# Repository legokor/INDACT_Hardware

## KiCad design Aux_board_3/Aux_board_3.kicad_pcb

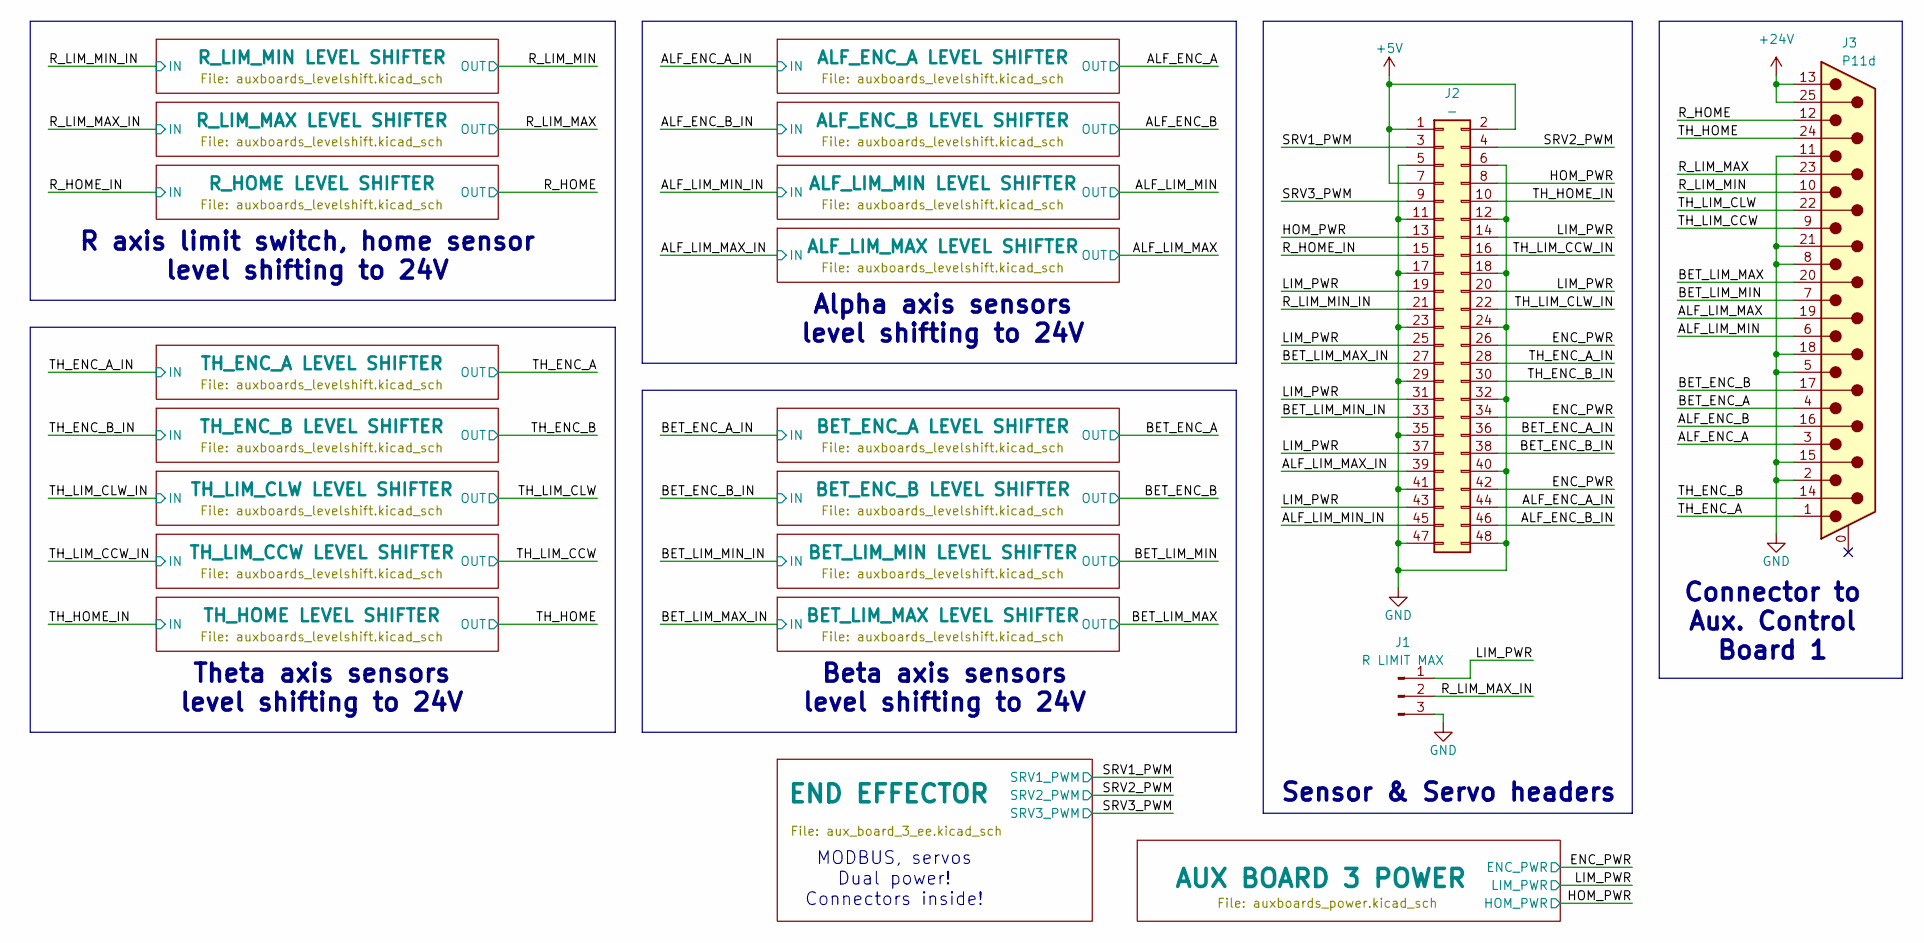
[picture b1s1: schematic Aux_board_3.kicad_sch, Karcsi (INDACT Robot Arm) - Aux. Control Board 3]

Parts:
J1: R LIMIT MAX; PinHeader_1x03_P2.54mm_Horizontal
J2: -; PinHeader_2x24_P2.54mm_Horizontal
J3: P11d; DSUB-25_Male_Horizontal_P2.77x2.84mm_EdgePinOffset7.70mm_Ho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

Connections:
+5V: J2.1, J2.2, J2.7; also elsewhere on the board
+24V: J3.13, J3.25; also elsewhere on the board
/ALF_ENC_A: J3.3; also elsewhere on the board
/ALF_ENC_A_IN: J2.44; also elsewhere on the board
/ALF_ENC_B: J3.16; also elsewhere on the board
/ALF_ENC_B_IN: J2.46; also elsewhere on the board
/ALF_LIM_MAX: J3.19; also elsewhere on the board
/ALF_LIM_MAX_IN: J2.39; also elsewhere on the board
/ALF_LIM_MIN: J3.6; also elsewhere on the board
/ALF_LIM_MIN_IN: J2.45; also elsewhere on the board
/BET_ENC_A: J3.4; also elsewhere on the board
/BET_ENC_A_IN: J2.36; also elsewhere on the board
/BET_ENC_B: J3.17; also elsewhere on the board
/BET_ENC_B_IN: J2.38; also elsewhere on the board
/BET_LIM_MAX: J3.20; also elsewhere on the board
/BET_LIM_MAX_IN: J2.27; also elsewhere on the board
/BET_LIM_MIN: J3.7; also elsewhere on the board
/BET_LIM_MIN_IN: J2.33; also elsewhere on the board
/ENC_PWR: J2.26, J2.34, J2.42; also elsewhere on the board
/HOM_PWR: J2.8, J2.13; also elsewhere on the board
/LIM_PWR: J1.1, J2.14, J2.19, J2.20, J2.25, J2.31, J2.37, J2.43; also elsewhere on the board
/R_HOME: J3.12; also elsewhere on the board
/R_HOME_IN: J2.15; also elsewhere on the board
/R_LIM_MAX: J3.23; also elsewhere on the board
/R_LIM_MAX_IN: J1.2; also elsewhere on the board
/R_LIM_MIN: J3.10; also elsewhere on the board
/R_LIM_MIN_IN: J2.21; also elsewhere on the board
/SRV1_PWM: J2.3; also elsewhere on the board
/SRV2_PWM: J2.4; also elsewhere on the board
/SRV3_PWM: J2.9; also elsewhere on the board
/TH_ENC_A: J3.1; also elsewhere on the board
/TH_ENC_A_IN: J2.28; also elsewhere on the board
/TH_ENC_B: J3.14; also elsewhere on the board
/TH_ENC_B_IN: J2.30; also elsewhere on the board
/TH_HOME: J3.24; also elsewhere on the board
/TH_HOME_IN: J2.10; also elsewhere on the board
/TH_LIM_CCW: J3.9; also elsewhere on the board
/TH_LIM_CCW_IN: J2.16; also elsewhere on the board
/TH_LIM_CLW: J3.22; also elsewhere on the board
/TH_LIM_CLW_IN: J2.22; also elsewhere on the board
GND: J1.3, J2.5, J2.6, J2.11, J2.12, J2.17, J2.18, J2.23, J2.24, J2.29, J2.32, J2.35, J2.40, J2.41, J2.47, J2.48, J3.2, J3.5, J3.8, J3.11, J3.15, J3.18, J3.21; also elsewhere on the board

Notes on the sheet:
Beta axis sensors level shifting to 24V
Sensor & Servo headers
Theta axis sensors level shifting to 24V
Alpha axis sensors level shifting to 24V
MODBUS, servos Dual power! Connectors inside!
R axis limit switch, home sensor level shifting to 24V
Connector to Aux. Control Board 1

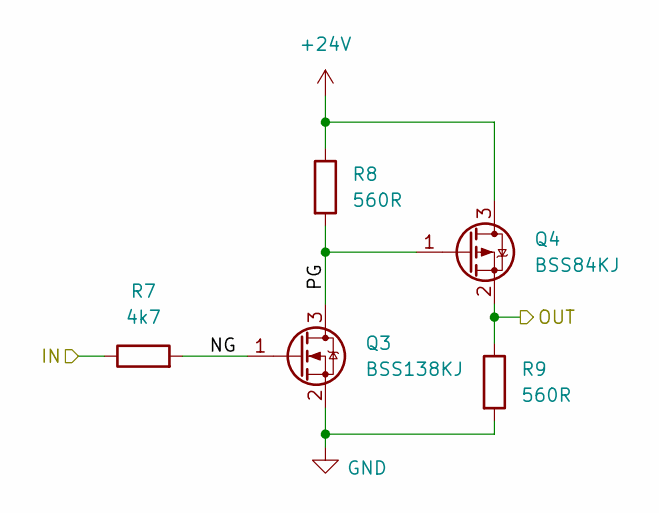
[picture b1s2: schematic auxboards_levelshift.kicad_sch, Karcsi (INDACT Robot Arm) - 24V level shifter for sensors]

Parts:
Q3: BSS138KJ; SOT-23
Q4: BSS84KJ; SOT-23
R7: 4k7; R_0805_2012Metric_Pad1.20x1.40mm_HandSolder
R8, R9: 560R; R_0805_2012Metric_Pad1.20x1.40mm_HandSolder

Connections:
+24V: Q4.3 (D), R8.1; also elsewhere on the board
/ALF_LIM_MIN: Q4.2 (S), R9.1; also elsewhere on the board
/ALF_LIM_MIN LEVEL SHIFTER/NG: Q3.1 (G), R7.2
/ALF_LIM_MIN LEVEL SHIFTER/PG: Q3.3 (D), Q4.1 (G), R8.2
/ALF_LIM_MIN_IN: R7.1; also elsewhere on the board
GND: Q3.2 (S), R9.2; also elsewhere on the board

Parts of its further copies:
Q1, Q5, Q7, Q9, Q11, Q13, Q15, Q17, Q19, Q21, Q23, Q25, Q27, Q29, Q31: BSS138KJ; SOT-23
Q2, Q6, Q8, Q10, Q12, Q14, Q16, Q18, Q20, Q22, Q24, Q26, Q28, Q30, Q32: BSS84KJ; SOT-23
R4, R10, R13, R16, R19, R22, R25, R28, R31, R34, R37, R40, R43, R46, R49: 4k7; R_0805_2012Metric_Pad1.20x1.40mm_HandSolder
R5, R6, R11, R12, R14, R15, R17, R18, R20, R21, R23, R24, R26, R27, R29, R30, R32, R33, R35, R36, R38, R39, R41, R42, R44, R45, R47, R48, R50, R51: 560R; R_0805_2012Metric_Pad1.20x1.40mm_HandSolder

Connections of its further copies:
+24V: Q2.3 (D), Q6.3 (D), Q8.3 (D), Q10.3 (D), Q12.3 (D), Q14.3 (D), Q16.3 (D), Q18.3 (D), Q20.3 (D), Q22.3 (D), Q24.3 (D), Q26.3 (D), Q28.3 (D), Q30.3 (D), Q32.3 (D), R5.1, R11.1, R14.1, R17.1, R20.1, R23.1, R26.1, R29.1, R32.1, R35.1, R38.1, R41.1, R44.1, R47.1, R50.1; also elsewhere on the board
/ALF_ENC_A: Q8.2 (S), R15.1; also elsewhere on the board
/ALF_ENC_A LEVEL SHIFTER/NG: Q7.1 (G), R13.2
/ALF_ENC_A LEVEL SHIFTER/PG: Q7.3 (D), Q8.1 (G), R14.2
/ALF_ENC_A_IN: R13.1; also elsewhere on the board
/ALF_ENC_B: Q6.2 (S), R12.1; also elsewhere on the board
/ALF_ENC_B LEVEL SHIFTER/NG: Q5.1 (G), R10.2
/ALF_ENC_B LEVEL SHIFTER/PG: Q5.3 (D), Q6.1 (G), R11.2
/ALF_ENC_B_IN: R10.1; also elsewhere on the board
/ALF_LIM_MAX: Q2.2 (S), R6.1; also elsewhere on the board
/ALF_LIM_MAX LEVEL SHIFTER/NG: Q1.1 (G), R4.2
/ALF_LIM_MAX LEVEL SHIFTER/PG: Q1.3 (D), Q2.1 (G), R5.2
/ALF_LIM_MAX_IN: R4.1; also elsewhere on the board
/BET_ENC_A: Q10.2 (S), R18.1; also elsewhere on the board
/BET_ENC_A LEVEL SHIFTER/NG: Q9.1 (G), R16.2
/BET_ENC_A LEVEL SHIFTER/PG: Q9.3 (D), Q10.1 (G), R17.2
/BET_ENC_A_IN: R16.1; also elsewhere on the board
/BET_ENC_B: Q12.2 (S), R21.1; also elsewhere on the board
/BET_ENC_B LEVEL SHIFTER/NG: Q11.1 (G), R19.2
/BET_ENC_B LEVEL SHIFTER/PG: Q11.3 (D), Q12.1 (G), R20.2
/BET_ENC_B_IN: R19.1; also elsewhere on the board
/BET_LIM_MAX: Q16.2 (S), R27.1; also elsewhere on the board
/BET_LIM_MAX LEVEL SHIFTER/NG: Q15.1 (G), R25.2
/BET_LIM_MAX LEVEL SHIFTER/PG: Q15.3 (D), Q16.1 (G), R26.2
/BET_LIM_MAX_IN: R25.1; also elsewhere on the board
/BET_LIM_MIN: Q14.2 (S), R24.1; also elsewhere on the board
/BET_LIM_MIN LEVEL SHIFTER/NG: Q13.1 (G), R22.2
/BET_LIM_MIN LEVEL SHIFTER/PG: Q13.3 (D), Q14.1 (G), R23.2
/BET_LIM_MIN_IN: R22.1; also elsewhere on the board
/R_HOME: Q32.2 (S), R51.1; also elsewhere on the board
/R_HOME LEVEL SHIFTER/NG: Q31.1 (G), R49.2
/R_HOME LEVEL SHIFTER/PG: Q31.3 (D), Q32.1 (G), R50.2
/R_HOME_IN: R49.1; also elsewhere on the board
/R_LIM_MAX: Q30.2 (S), R48.1; also elsewhere on the board
/R_LIM_MAX LEVEL SHIFTER/NG: Q29.1 (G), R46.2
/R_LIM_MAX LEVEL SHIFTER/PG: Q29.3 (D), Q30.1 (G), R47.2
/R_LIM_MAX_IN: R46.1; also elsewhere on the board
/R_LIM_MIN: Q28.2 (S), R45.1; also elsewhere on the board
/R_LIM_MIN LEVEL SHIFTER/NG: Q27.1 (G), R43.2
/R_LIM_MIN LEVEL SHIFTER/PG: Q27.3 (D), Q28.1 (G), R44.2
/R_LIM_MIN_IN: R43.1; also elsewhere on the board
/TH_ENC_A: Q18.2 (S), R30.1; also elsewhere on the board
/TH_ENC_A LEVEL SHIFTER/NG: Q17.1 (G), R28.2
/TH_ENC_A LEVEL SHIFTER/PG: Q17.3 (D), Q18.1 (G), R29.2
/TH_ENC_A_IN: R28.1; also elsewhere on the board
/TH_ENC_B: Q20.2 (S), R33.1; also elsewhere on the board
/TH_ENC_B LEVEL SHIFTER/NG: Q19.1 (G), R31.2
/TH_ENC_B LEVEL SHIFTER/PG: Q19.3 (D), Q20.1 (G), R32.2
/TH_ENC_B_IN: R31.1; also elsewhere on the board
/TH_HOME: Q26.2 (S), R42.1; also elsewhere on the board
/TH_HOME LEVEL SHIFTER/NG: Q25.1 (G), R40.2
/TH_HOME LEVEL SHIFTER/PG: Q25.3 (D), Q26.1 (G), R41.2
/TH_HOME_IN: R40.1; also elsewhere on the board
/TH_LIM_CCW: Q24.2 (S), R39.1; also elsewhere on the board
/TH_LIM_CCW LEVEL SHIFTER/NG: Q23.1 (G), R37.2
/TH_LIM_CCW LEVEL SHIFTER/PG: Q23.3 (D), Q24.1 (G), R38.2
/TH_LIM_CCW_IN: R37.1; also elsewhere on the board
/TH_LIM_CLW: Q22.2 (S), R36.1; also elsewhere on the board
/TH_LIM_CLW LEVEL SHIFTER/NG: Q21.1 (G), R34.2
/TH_LIM_CLW LEVEL SHIFTER/PG: Q21.3 (D), Q22.1 (G), R35.2
/TH_LIM_CLW_IN: R34.1; also elsewhere on the board
GND: Q1.2 (S), Q5.2 (S), Q7.2 (S), Q9.2 (S), Q11.2 (S), Q13.2 (S), Q15.2 (S), Q17.2 (S), Q19.2 (S), Q21.2 (S), Q23.2 (S), Q25.2 (S), Q27.2 (S), Q29.2 (S), Q31.2 (S), R6.2, R12.2, R15.2, R18.2, R21.2, R24.2, R27.2, R30.2, R33.2, R36.2, R39.2, R42.2, R45.2, R48.2, R51.2; also elsewhere on the board

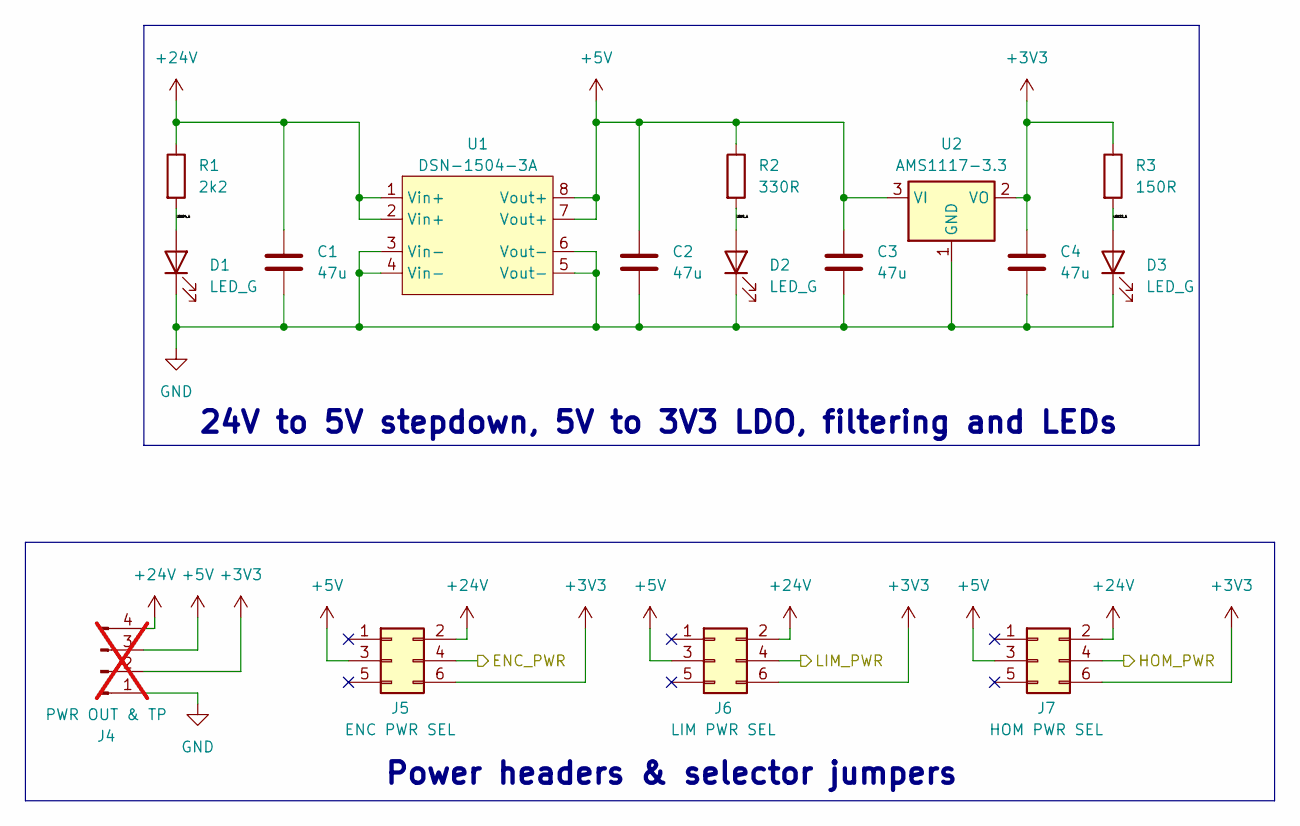
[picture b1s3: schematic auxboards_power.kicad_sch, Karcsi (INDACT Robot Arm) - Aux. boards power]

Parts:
C1, C2, C3, C4: 47u; C_0805_2012Metric_Pad1.18x1.45mm_HandSolder
D1, D2, D3: LED_G; LED_0805_2012Metric_Pad1.15x1.40mm_HandSolder
J4: PWR OUT & TP; PinHeader_1x04_P2.54mm_Vertical; not fitted
J5: ENC PWR SEL; PinHeader_2x03_P2.54mm_Vertical
J6: LIM PWR SEL; PinHeader_2x03_P2.54mm_Vertical
J7: HOM PWR SEL; PinHeader_2x03_P2.54mm_Vertical
R1: 2k2; R_0805_2012Metric_Pad1.20x1.40mm_HandSolder
R2: 330R; R_0805_2012Metric_Pad1.20x1.40mm_HandSolder
R3: 150R; R_0805_2012Metric_Pad1.20x1.40mm_HandSolder
U1: DSN-1504-3A
U2: AMS1117-3.3; SOT-223-3_TabPin2

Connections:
+3V3: C4.1, J4.2, J5.6, J6.6, J7.6, R3.1, U2.2 (VO)
+5V: C2.1, C3.1, J4.3, J5.3, J6.3, J7.3, R2.1, U1.7 (Vout+), U1.8 (Vout+), U2.3 (VI); also elsewhere on the board
+24V: C1.1, J4.4, J5.2, J6.2, J7.2, R1.1, U1.1 (Vin+), U1.2 (Vin+); also elsewhere on the board
/AUX BOARD 3 POWER/LED5_A: D2.2 (A), R2.2
/AUX BOARD 3 POWER/LED24_A: D1.2 (A), R1.2
/AUX BOARD 3 POWER/LED33_A: D3.2 (A), R3.2
/ENC_PWR: J5.4; also elsewhere on the board
/HOM_PWR: J7.4; also elsewhere on the board
/LIM_PWR: J6.4; also elsewhere on the board
GND: C1.2, C2.2, C3.2, C4.2, D1.1 (K), D2.1 (K), D3.1 (K), J4.1, U1.3 (Vin-), U1.4 (Vin-), U1.5 (Vout-), U1.6 (Vout-), U2.1 (GND); also elsewhere on the board

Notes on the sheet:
Power headers & selector jumpers
24V to 5V stepdown, 5V to 3V3 LDO, filtering and LEDs

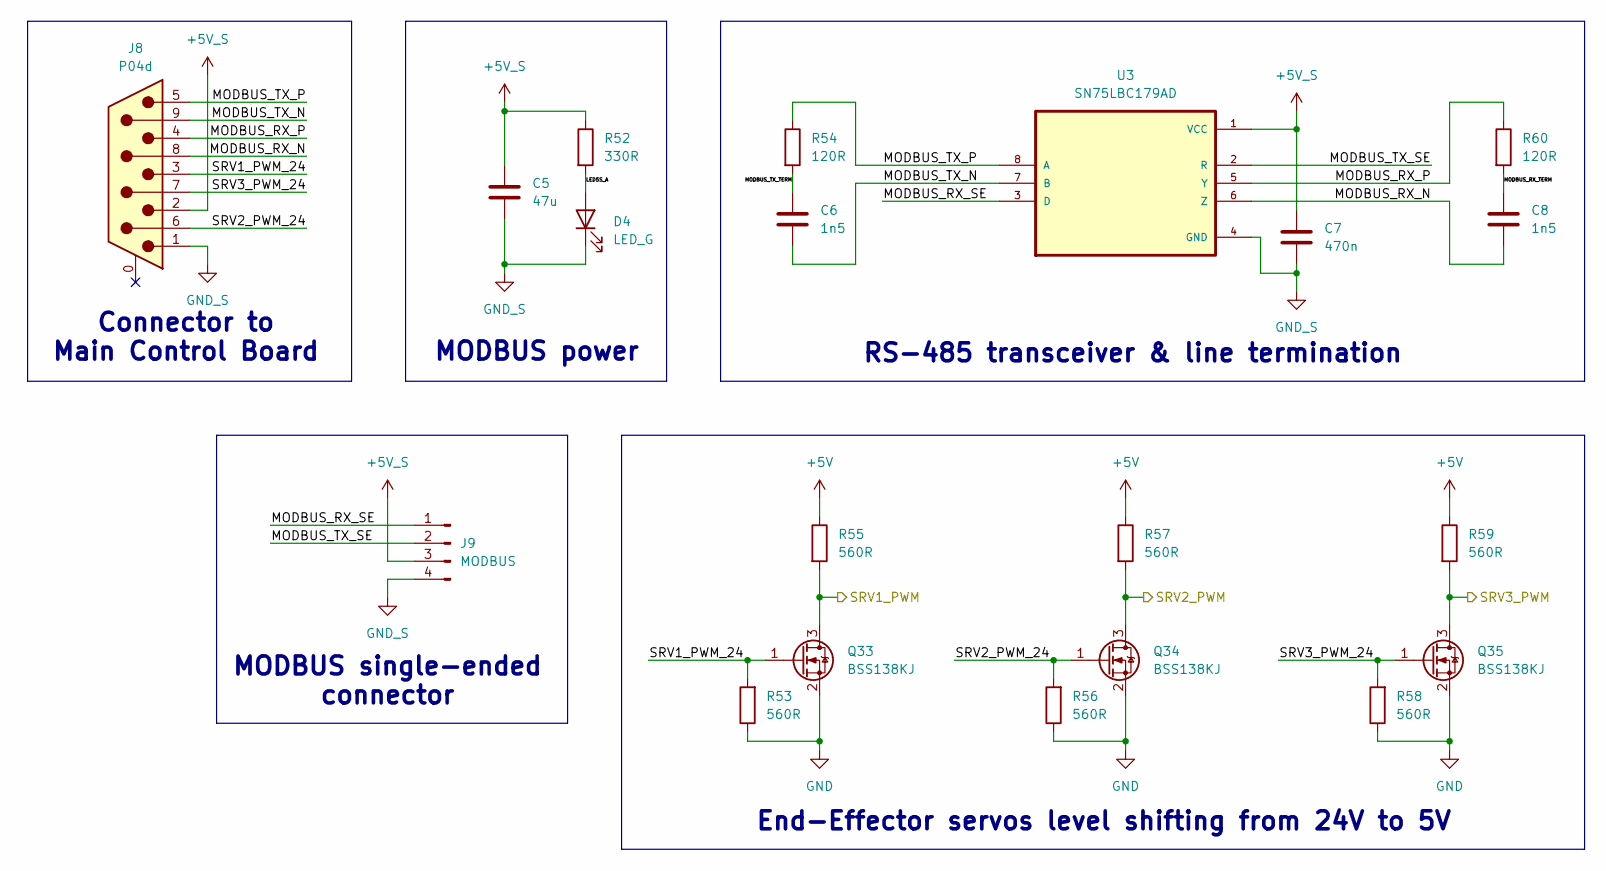
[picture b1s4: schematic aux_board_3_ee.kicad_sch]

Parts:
C5: 47u; C_0805_2012Metric_Pad1.18x1.45mm_HandSolder
C6, C8: 1n5; C_0805_2012Metric_Pad1.18x1.45mm_HandSolder
C7: 470n; C_0805_2012Metric_Pad1.18x1.45mm_HandSolder
D4: LED_G; LED_0805_2012Metric_Pad1.15x1.40mm_HandSolder
J8: P04d; DSUB-9_Male_Horizontal_P2.77x2.84mm_EdgePinOffset7.70mm_Hou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
J9: MODBUS; PinHeader_1x04_P2.54mm_Horizontal
Q33, Q34, Q35: BSS138KJ; SOT-23
R52: 330R; R_0805_2012Metric_Pad1.20x1.40mm_HandSolder
R53, R55, R56, R57, R58, R59: 560R; R_0805_2012Metric_Pad1.20x1.40mm_HandSolder
R54, R60: 120R; R_0805_2012Metric_Pad1.20x1.40mm_HandSolder
U3: SN75LBC179AD; SOIC127P599X175-8N

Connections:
+5V: R55.1, R57.1, R59.1; also elsewhere on the board
+5V_S: C5.1, C7.1, J8.2, J9.3, R52.1, U3.1 (VCC)
/END EFFECTOR/LED5S_A: D4.2 (A), R52.2
/END EFFECTOR/MODBUS_RX_N: C8.2, J8.8, U3.6 (Z)
/END EFFECTOR/MODBUS_RX_P: J8.4, R60.1, U3.5 (Y)
/END EFFECTOR/MODBUS_RX_SE: J9.1, U3.3 (D)
/END EFFECTOR/MODBUS_RX_TERM: C8.1, R60.2
/END EFFECTOR/MODBUS_TX_N: C6.2, J8.9, U3.7 (B)
/END EFFECTOR/MODBUS_TX_P: J8.5, R54.1, U3.8 (A)
/END EFFECTOR/MODBUS_TX_SE: J9.2, U3.2 (R)
/END EFFECTOR/MODBUS_TX_TERM: C6.1, R54.2
/END EFFECTOR/SRV1_PWM_24: J8.3, Q33.1 (G), R53.2
/END EFFECTOR/SRV2_PWM_24: J8.6, Q34.1 (G), R56.2
/END EFFECTOR/SRV3_PWM_24: J8.7, Q35.1 (G), R58.2
/SRV1_PWM: Q33.3 (D), R55.2; also elsewhere on the board
/SRV2_PWM: Q34.3 (D), R57.2; also elsewhere on the board
/SRV3_PWM: Q35.3 (D), R59.2; also elsewhere on the board
GND: Q33.2 (S), Q34.2 (S), Q35.2 (S), R53.1, R56.1, R58.1; also elsewhere on the board
GND_S: C5.2, C7.2, D4.1 (K), J8.1, J9.4, U3.4 (GND)

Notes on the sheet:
End-Effector servos level shifting from 24V to 5V
RS-485 transceiver & line termination
Connector to Main Control Board
MODBUS power
MODBUS single-ended connector

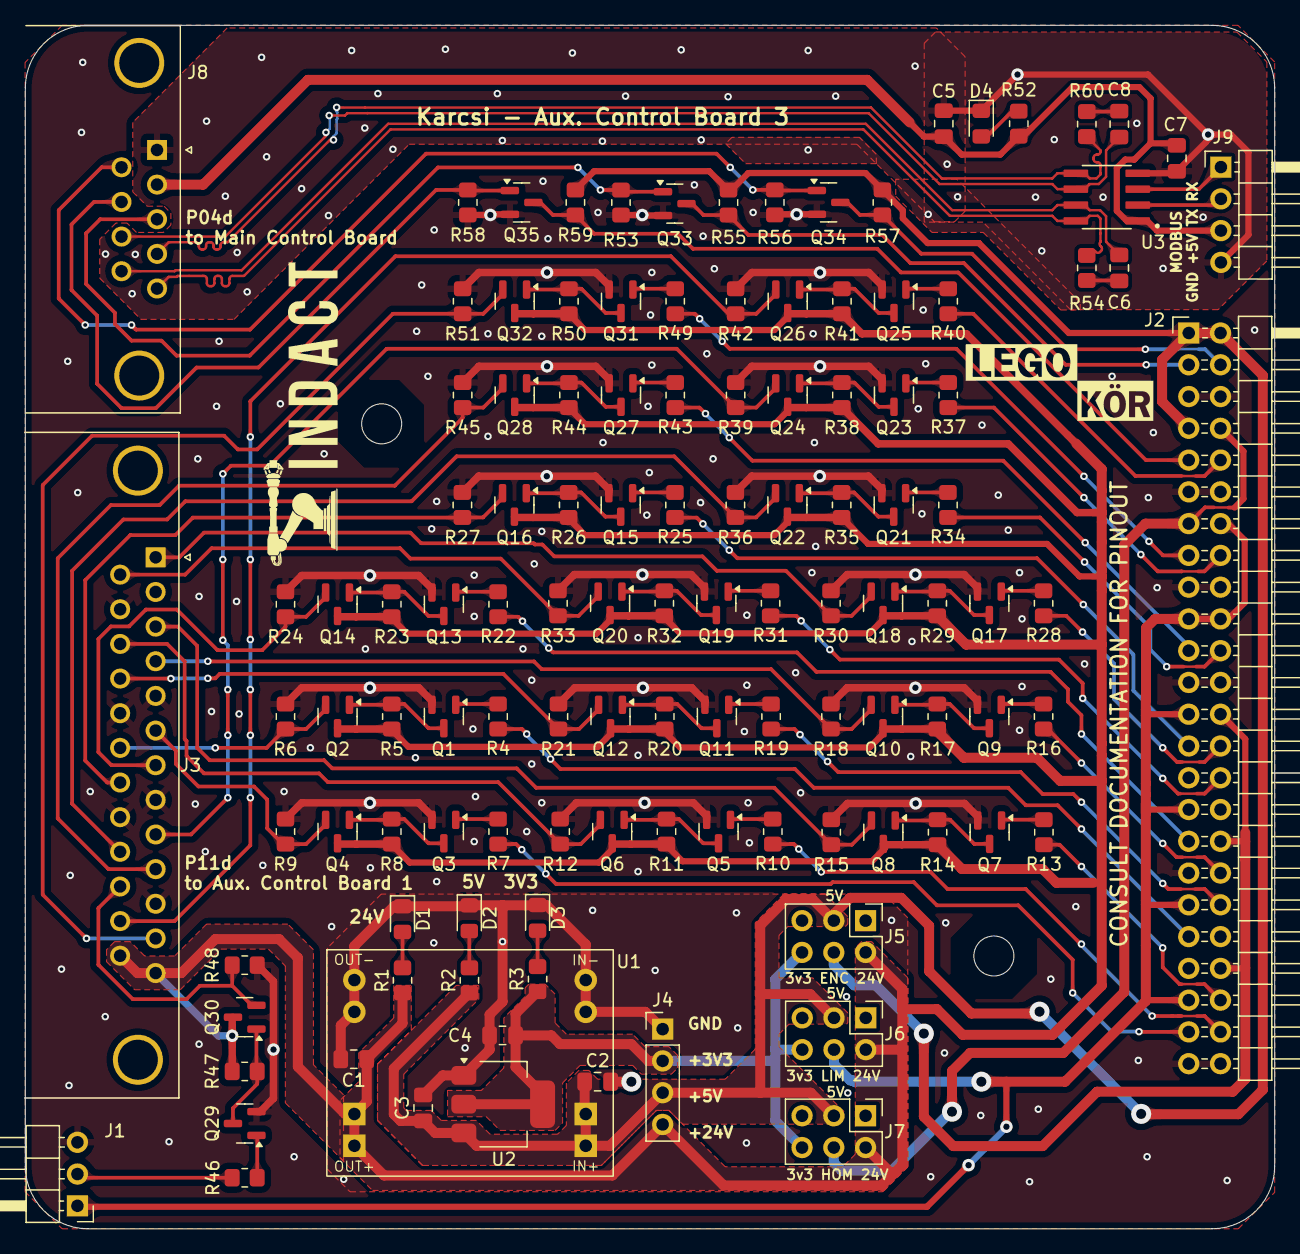
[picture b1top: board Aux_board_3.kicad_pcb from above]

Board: 2 copper layers, 99.9 x 96.2 mm, 119 parts (0 on the bottom side), 91 nets.

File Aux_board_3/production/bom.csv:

Designator,Footprint,Quantity,Value,LCSC Part #
"C1, C2, C3, C4, C5",0805,5,47u,
"C6, C8",0805,2,1n5,
C7,0805,1,470n,
"D1, D2, D3, D4",0805,4,LED_G,
J1,PinHeader_1x03_P2.54mm_Horizontal,1,R LIMIT MAX,
J2,PinHeader_2x24_P2.54mm_Horizontal,1,-,
J3,DSUB-25_Male_Horizontal_P2.77x2.84mm_EdgePinOffset7.70mm_Housed_MountingHolesOffset9.12mm,1,P11d,
J5,PinHeader_2x03_P2.54mm_Vertical,1,ENC PWR SEL,
J6,PinHeader_2x03_P2.54mm_Vertical,1,LIM PWR SEL,
J7,PinHeader_2x03_P2.54mm_Vertical,1,HOM PWR SEL,
J8,DSUB-9_Male_Horizontal_P2.77x2.84mm_EdgePinOffset7.70mm_Housed_MountingHolesOffset9.12mm,1,P04d,
J9,PinHeader_1x04_P2.54mm_Horizontal,1,MODBUS,
"Q1, Q11, Q13, Q15, Q17, Q19, Q21, Q23, Q25, Q27, Q29, Q3, Q31, Q33, Q34, Q35, Q5, Q7, Q9",SOT-23,19,BSS138KJ,
"Q10, Q12, Q14, Q16, Q18, Q2, Q20, Q22, Q24, Q26, Q28, Q30, Q32, Q4, Q6, Q8",SOT-23,16,BSS84KJ,
R1,0805,1,2k2,
"R10, R13, R16, R19, R22, R25, R28, R31, R34, R37, R4, R40, R43, R46, R49, R7",0805,16,4k7,
"R11, R12, R14, R15, R17, R18, R20, R21, R23, R24, R26, R27, R29, R30, R32, R33, R35, R36, R38, R39, R41, R42, R44, R45, R47, R48, R5, R50, R51, R53, R55, R56, R57, R58, R59, R6, R8, R9",0805,38,560R,
"R2, R52",0805,2,330R,
R3,0805,1,150R,
"R54, R60",0805,2,120R,
U1,DSN-1504-3A,1,DSN-1504-3A,
U2,SOT-223-3_TabPin2,1,AMS1117-3.3,
U3,SOIC127P599X175-8N,1,SN75LBC179AD,

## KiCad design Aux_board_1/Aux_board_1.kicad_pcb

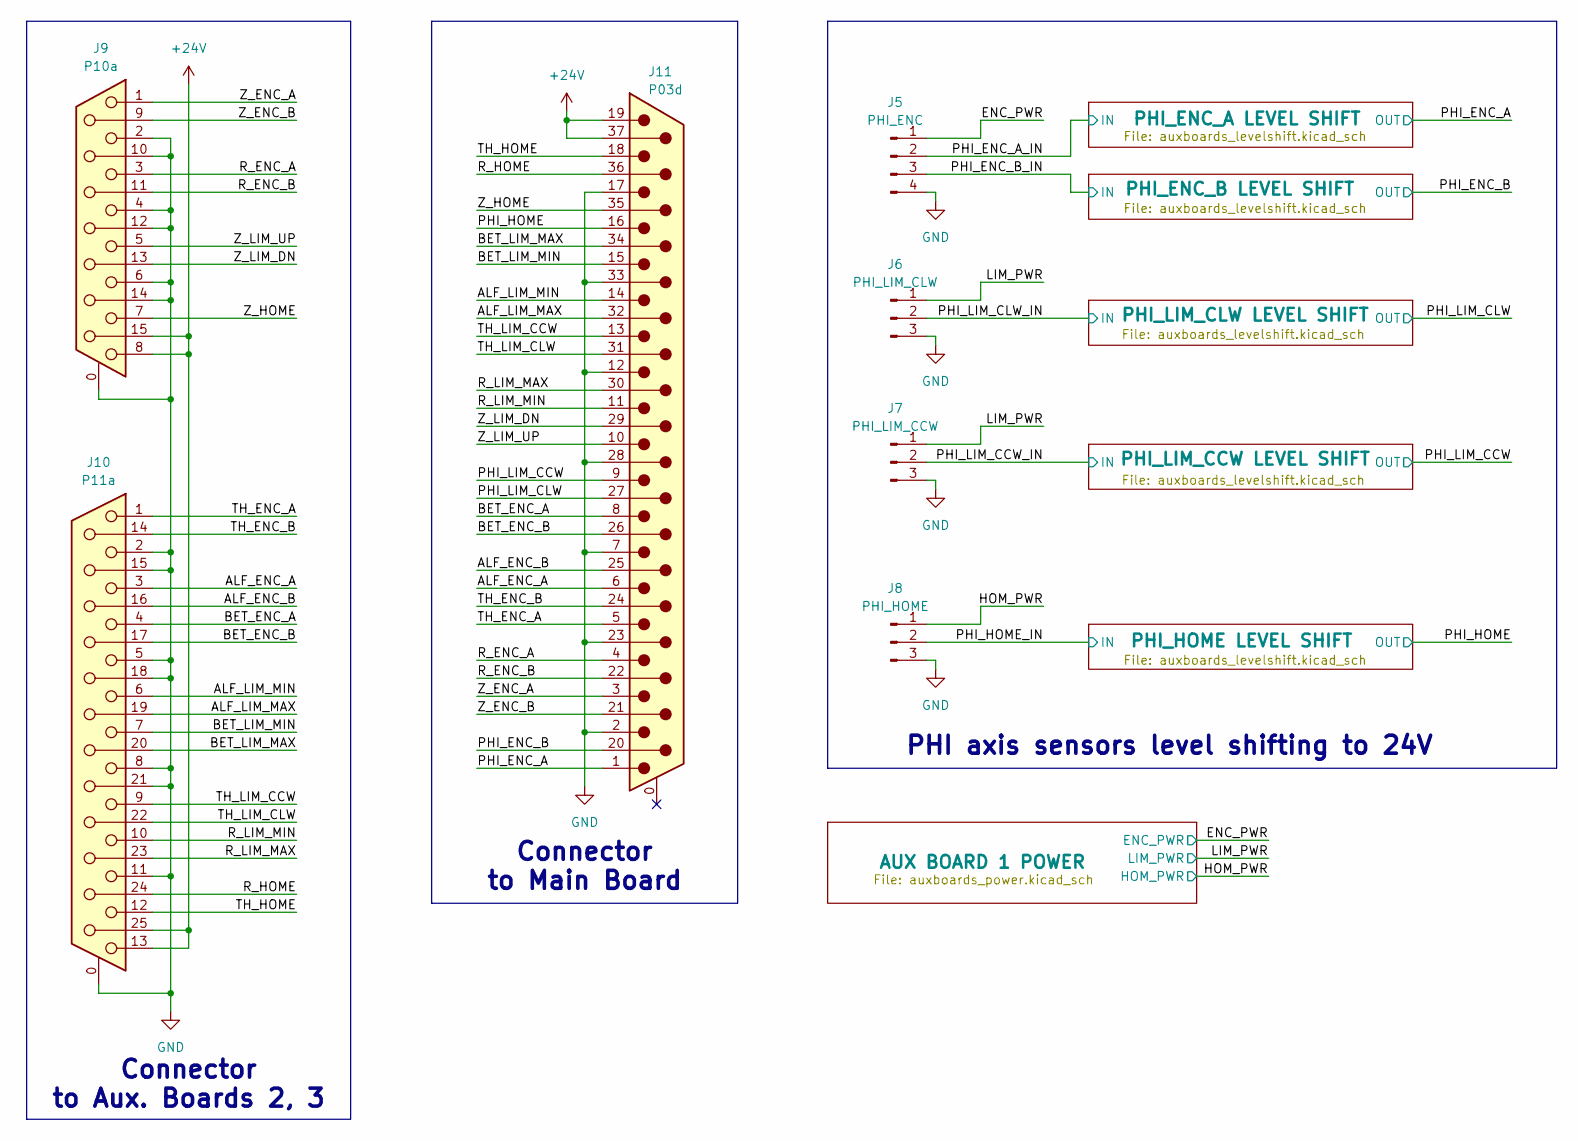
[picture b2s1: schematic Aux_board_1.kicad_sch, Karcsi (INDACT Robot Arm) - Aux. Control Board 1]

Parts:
J5: PHI_ENC; PinHeader_1x04_P2.54mm_Horizontal
J6: PHI_LIM_CLW; PinHeader_1x03_P2.54mm_Horizontal
J7: PHI_LIM_CCW; PinHeader_1x03_P2.54mm_Horizontal
J8: PHI_HOME; PinHeader_1x03_P2.54mm_Horizontal
J9: P10a; DSUB-15_Female_Horizontal_P2.77x2.84mm_EdgePinOffset7.70mm_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
J10: P11a; DSUB-25_Female_Horizontal_P2.77x2.84mm_EdgePinOffset7.70mm_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
J11: P03d; DSUB-37_Male_Horizontal_P2.77x2.84mm_EdgePinOffset7.70mm_Ho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

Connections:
+24V: J9.8, J9.15, J10.13, J10.25, J11.19, J11.37; also elsewhere on the board
/ALF_ENC_A: J10.3, J11.6
/ALF_ENC_B: J10.16, J11.25
/ALF_LIM_MAX: J10.19, J11.32
/ALF_LIM_MIN: J10.6, J11.14
/BET_ENC_A: J10.4, J11.8
/BET_ENC_B: J10.17, J11.26
/BET_LIM_MAX: J10.20, J11.34
/BET_LIM_MIN: J10.7, J11.15
/ENC_PWR: J5.1; also elsewhere on the board
/HOM_PWR: J8.1; also elsewhere on the board
/LIM_PWR: J6.1, J7.1; also elsewhere on the board
/PHI_ENC_A: J11.1; also elsewhere on the board
/PHI_ENC_A_IN: J5.2; also elsewhere on the board
/PHI_ENC_B: J11.20; also elsewhere on the board
/PHI_ENC_B_IN: J5.3; also elsewhere on the board
/PHI_HOME: J11.16; also elsewhere on the board
/PHI_HOME_IN: J8.2; also elsewhere on the board
/PHI_LIM_CCW: J11.9; also elsewhere on the board
/PHI_LIM_CCW_IN: J7.2; also elsewhere on the board
/PHI_LIM_CLW: J11.27; also elsewhere on the board
/PHI_LIM_CLW_IN: J6.2; also elsewhere on the board
/R_ENC_A: J9.3, J11.4
/R_ENC_B: J9.11 (P111), J11.22
/R_HOME: J10.24, J11.36
/R_LIM_MAX: J10.23, J11.30
/R_LIM_MIN: J10.10, J11.11
/TH_ENC_A: J10.1, J11.5
/TH_ENC_B: J10.14, J11.24
/TH_HOME: J10.12, J11.18
/TH_LIM_CCW: J10.9, J11.13
/TH_LIM_CLW: J10.22, J11.31
/Z_ENC_A: J9.1, J11.3
/Z_ENC_B: J9.9, J11.21
/Z_HOME: J9.7, J11.35
/Z_LIM_DN: J9.13, J11.29
/Z_LIM_UP: J9.5, J11.10
GND: J5.4, J6.3, J7.3, J8.3, J9.0 (PAD), J9.2, J9.4, J9.6, J9.10, J9.12, J9.14, J10.0 (PAD), J10.2, J10.5, J10.8, J10.11, J10.15, J10.18, J10.21, J11.2, J11.7, J11.12, J11.17, J11.23, J11.28, J11.33; also elsewhere on the board

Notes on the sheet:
Connector to Main Board
Connector to Aux. Boards 2, 3
PHI axis sensors level shifting to 24V

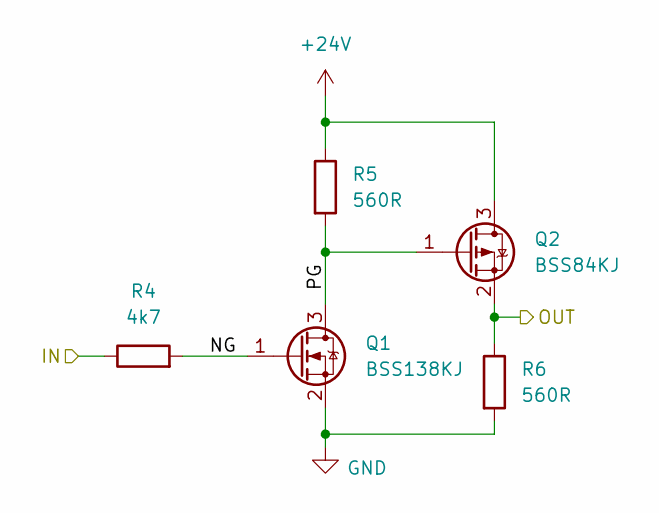
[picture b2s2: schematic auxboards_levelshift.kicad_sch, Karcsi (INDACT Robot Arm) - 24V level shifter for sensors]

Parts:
Q1: BSS138KJ; SOT-23
Q2: BSS84KJ; SOT-23
R4: 4k7; R_0805_2012Metric_Pad1.20x1.40mm_HandSolder
R5, R6: 560R; R_0805_2012Metric_Pad1.20x1.40mm_HandSolder

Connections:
+24V: Q2.3 (D), R5.1; also elsewhere on the board
/PHI_ENC_A: Q2.2 (S), R6.1; also elsewhere on the board
/PHI_ENC_A LEVEL SHIFT/NG: Q1.1 (G), R4.2
/PHI_ENC_A LEVEL SHIFT/PG: Q1.3 (D), Q2.1 (G), R5.2
/PHI_ENC_A_IN: R4.1; also elsewhere on the board
GND: Q1.2 (S), R6.2; also elsewhere on the board

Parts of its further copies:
Q3, Q5, Q7, Q9: BSS138KJ; SOT-23
Q4, Q6, Q8, Q10: BSS84KJ; SOT-23
R7, R10, R13, R16: 4k7; R_0805_2012Metric_Pad1.20x1.40mm_HandSolder
R8, R9, R11, R12, R14, R15, R17, R18: 560R; R_0805_2012Metric_Pad1.20x1.40mm_HandSolder

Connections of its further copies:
+24V: Q4.3 (D), Q6.3 (D), Q8.3 (D), Q10.3 (D), R8.1, R11.1, R14.1, R17.1; also elsewhere on the board
/PHI_ENC_B: Q4.2 (S), R9.1; also elsewhere on the board
/PHI_ENC_B LEVEL SHIFT/NG: Q3.1 (G), R7.2
/PHI_ENC_B LEVEL SHIFT/PG: Q3.3 (D), Q4.1 (G), R8.2
/PHI_ENC_B_IN: R7.1; also elsewhere on the board
/PHI_HOME: Q10.2 (S), R18.1; also elsewhere on the board
/PHI_HOME LEVEL SHIFT/NG: Q9.1 (G), R16.2
/PHI_HOME LEVEL SHIFT/PG: Q9.3 (D), Q10.1 (G), R17.2
/PHI_HOME_IN: R16.1; also elsewhere on the board
/PHI_LIM_CCW: Q8.2 (S), R15.1; also elsewhere on the board
/PHI_LIM_CCW LEVEL SHIFT/NG: Q7.1 (G), R13.2
/PHI_LIM_CCW LEVEL SHIFT/PG: Q7.3 (D), Q8.1 (G), R14.2
/PHI_LIM_CCW_IN: R13.1; also elsewhere on the board
/PHI_LIM_CLW: Q6.2 (S), R12.1; also elsewhere on the board
/PHI_LIM_CLW LEVEL SHIFT/NG: Q5.1 (G), R10.2
/PHI_LIM_CLW LEVEL SHIFT/PG: Q5.3 (D), Q6.1 (G), R11.2
/PHI_LIM_CLW_IN: R10.1; also elsewhere on the board
GND: Q3.2 (S), Q5.2 (S), Q7.2 (S), Q9.2 (S), R9.2, R12.2, R15.2, R18.2; also elsewhere on the board

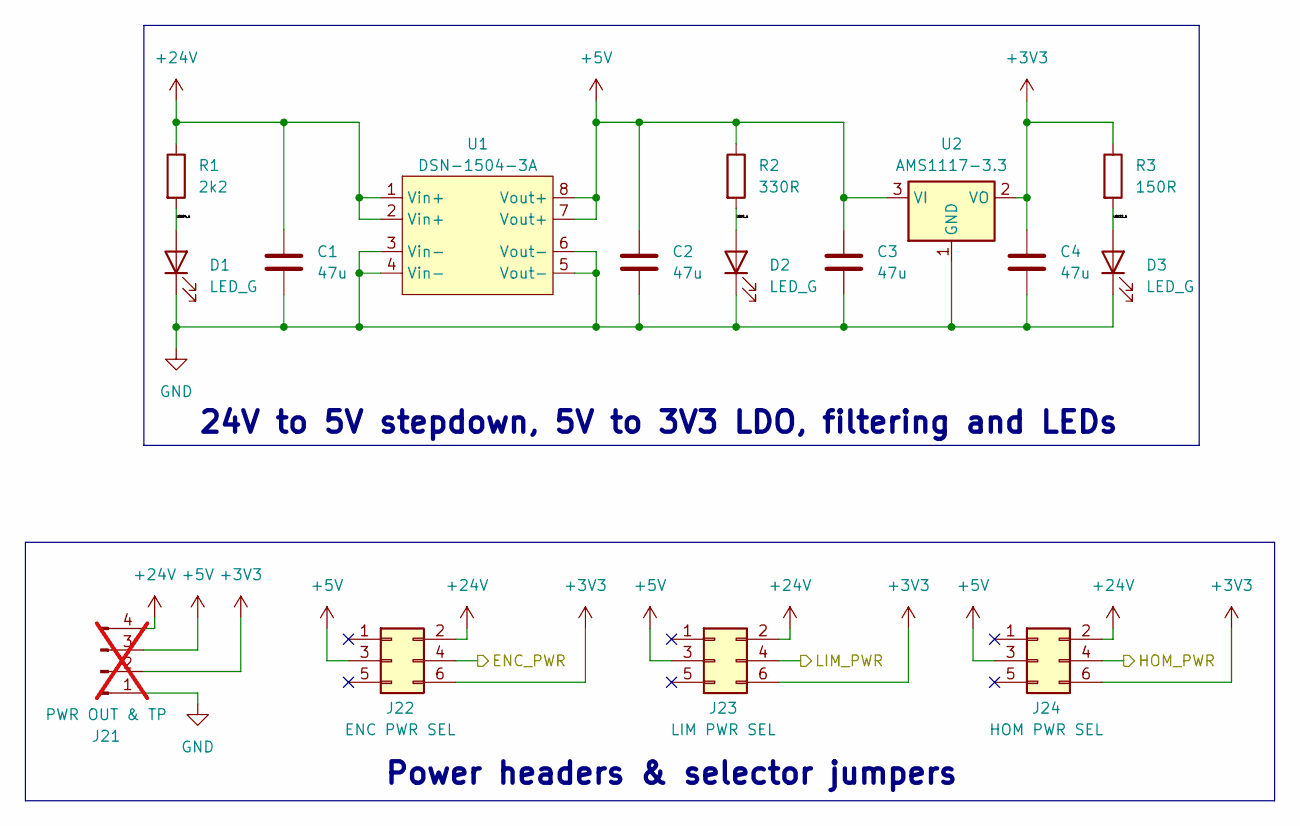
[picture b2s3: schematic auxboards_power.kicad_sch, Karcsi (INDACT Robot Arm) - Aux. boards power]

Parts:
C1, C2, C3, C4: 47u; C_0805_2012Metric_Pad1.18x1.45mm_HandSolder
D1, D2, D3: LED_G; LED_0805_2012Metric_Pad1.15x1.40mm_HandSolder
J21: PWR OUT & TP; PinHeader_1x04_P2.54mm_Vertical; not fitted
J22: ENC PWR SEL; PinHeader_2x03_P2.54mm_Vertical
J23: LIM PWR SEL; PinHeader_2x03_P2.54mm_Vertical
J24: HOM PWR SEL; PinHeader_2x03_P2.54mm_Vertical
R1: 2k2; R_0805_2012Metric_Pad1.20x1.40mm_HandSolder
R2: 330R; R_0805_2012Metric_Pad1.20x1.40mm_HandSolder
R3: 150R; R_0805_2012Metric_Pad1.20x1.40mm_HandSolder
U1: DSN-1504-3A
U2: AMS1117-3.3; SOT-223-3_TabPin2

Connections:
+3V3: C4.1, R3.1, U2.2 (VO); also elsewhere on the board
+5V: C2.1, C3.1, R2.1, U1.7 (Vout+), U1.8 (Vout+), U2.3 (VI); also elsewhere on the board
+24V: C1.1, R1.1, U1.1 (Vin+), U1.2 (Vin+); also elsewhere on the board
/AUX BOARD 1 POWER/LED5_A: D2.2 (A), R2.2
/AUX BOARD 1 POWER/LED24_A: D1.2 (A), R1.2
/AUX BOARD 1 POWER/LED33_A: D3.2 (A), R3.2
GND: C1.2, C2.2, C3.2, C4.2, D1.1 (K), D2.1 (K), D3.1 (K), U1.3 (Vin-), U1.4 (Vin-), U1.5 (Vout-), U1.6 (Vout-), U2.1 (GND); also elsewhere on the board

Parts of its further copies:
J1: PWR OUT & TP; PinHeader_1x04_P2.54mm_Vertical; not fitted
J2: ENC PWR SEL; PinHeader_2x03_P2.54mm_Vertical
J3: LIM PWR SEL; PinHeader_2x03_P2.54mm_Vertical
J4: HOM PWR SEL; PinHeader_2x03_P2.54mm_Vertical

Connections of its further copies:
+3V3: J1.2, J2.6, J3.6, J4.6; also elsewhere on the board
+5V: J1.3, J2.3, J3.3, J4.3; also elsewhere on the board
+24V: J1.4, J2.2, J3.2, J4.2; also elsewhere on the board
/ENC_PWR: J2.4; also elsewhere on the board
/HOM_PWR: J4.4; also elsewhere on the board
/LIM_PWR: J3.4; also elsewhere on the board
GND: J1.1; also elsewhere on the board

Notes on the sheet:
Power headers & selector jumpers
24V to 5V stepdown, 5V to 3V3 LDO, filtering and LEDs

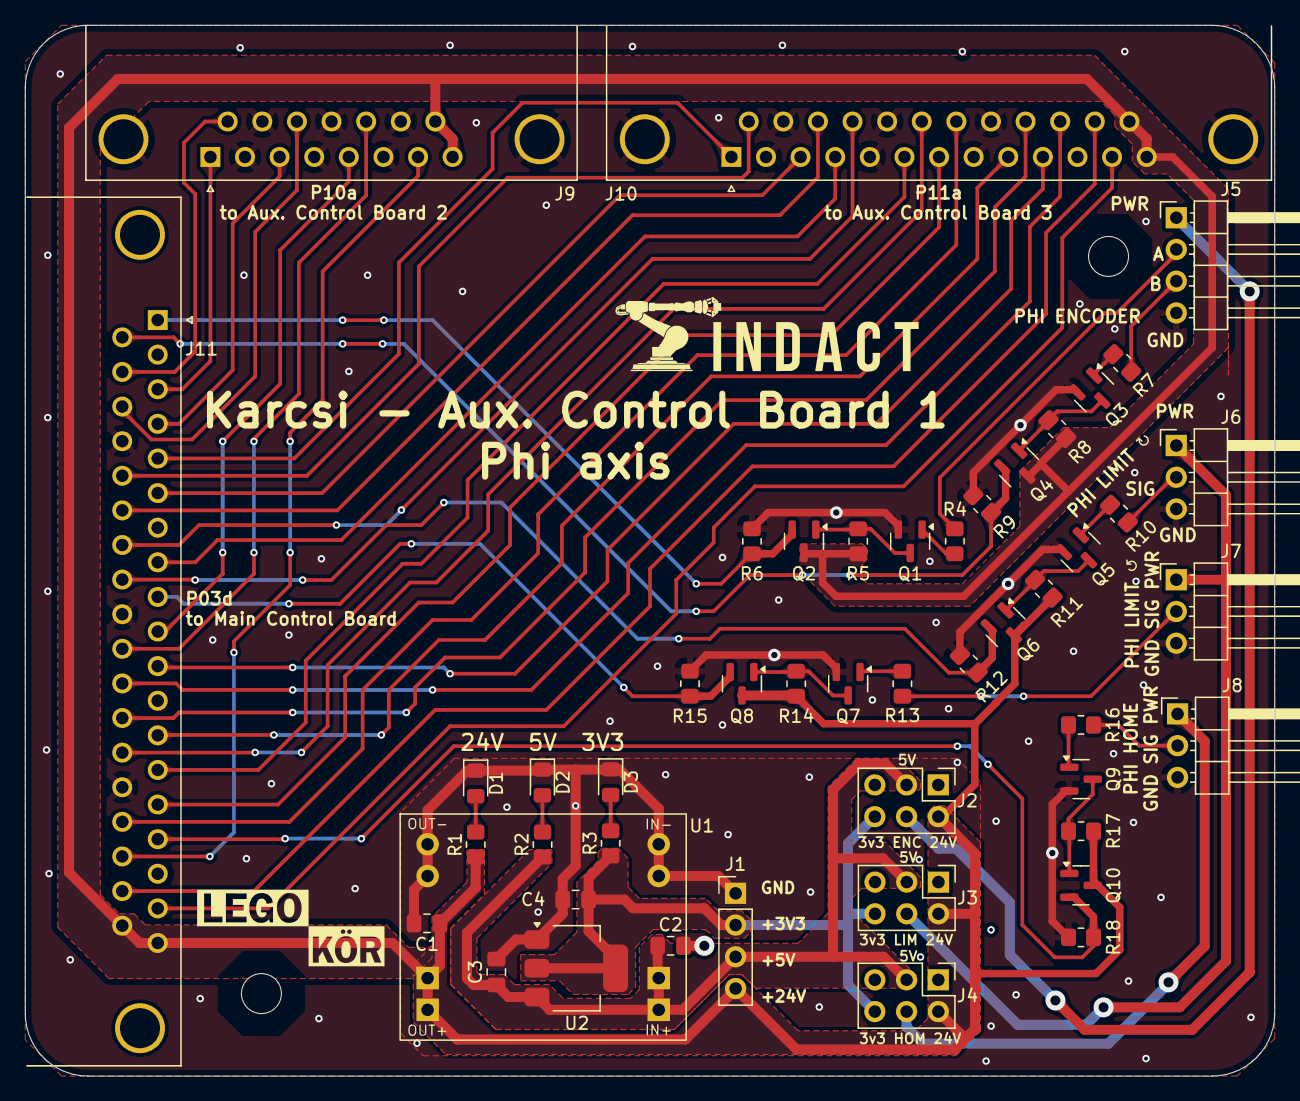
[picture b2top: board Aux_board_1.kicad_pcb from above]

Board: 2 copper layers, 100.0 x 84.1 mm, 48 parts (0 on the bottom side), 53 nets.

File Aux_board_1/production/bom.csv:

Designator,Footprint,Quantity,Value,LCSC Part #
"C1, C2, C3, C4",0805,4,47u,
"D1, D2, D3",0805,3,LED_G,
J10,DSUB-25_Female_Horizontal_P2.77x2.84mm_EdgePinOffset7.70mm_Housed_MountingHolesOffset9.12mm,1,P11a,
J11,DSUB-37_Male_Horizontal_P2.77x2.84mm_EdgePinOffset7.70mm_Housed_MountingHolesOffset9.12mm,1,P03d,
J2,PinHeader_2x03_P2.54mm_Vertical,1,ENC PWR SEL,
J3,PinHeader_2x03_P2.54mm_Vertical,1,LIM PWR SEL,
J4,PinHeader_2x03_P2.54mm_Vertical,1,HOM PWR SEL,
J5,PinHeader_1x04_P2.54mm_Horizontal,1,PHI_ENC,
J6,PinHeader_1x03_P2.54mm_Horizontal,1,PHI_LIM_CLW,
J7,PinHeader_1x03_P2.54mm_Horizontal,1,PHI_LIM_CCW,
J8,PinHeader_1x03_P2.54mm_Horizontal,1,PHI_HOME,
J9,DSUB-15_Female_Horizontal_P2.77x2.84mm_EdgePinOffset7.70mm_Housed_MountingHolesOffset9.12mm,1,P10a,
"Q1, Q3, Q5, Q7, Q9",SOT-23,5,BSS138KJ,
"Q10, Q2, Q4, Q6, Q8",SOT-23,5,BSS84KJ,
R1,0805,1,2k2,
"R10, R13, R16, R4, R7",0805,5,4k7,
"R11, R12, R14, R15, R17, R18, R5, R6, R8, R9",0805,10,560R,
R2,0805,1,330R,
R3,0805,1,150R,
U1,DSN-1504-3A,1,DSN-1504-3A,
U2,SOT-223-3_TabPin2,1,AMS1117-3.3,
